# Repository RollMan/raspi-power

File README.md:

# Raspi-Power
## What is this?
This circuit keeps power supply to a raspberry pi for a second after the main power is down to shut down safely.. The functionalities are almost same as a UPS, but this is specialized to mount a car. This is useful for broadcasting your driving scenary, for example.

## How it works?
A car has two (strictly three) outlets: direct to battery and ACC. After you turn off an engine, ACC also turns off. This circuit detects that, and keep the power from battery directly while the raspberry pi is shutting down.

## Environment
- [kicad](http://kicad-pcb.org/) to see this circuit

## Misc
- A OKL\_T footprint thanks to (stm32f1/stm32-board)[https://github.com/stm32f1/stm32_board]

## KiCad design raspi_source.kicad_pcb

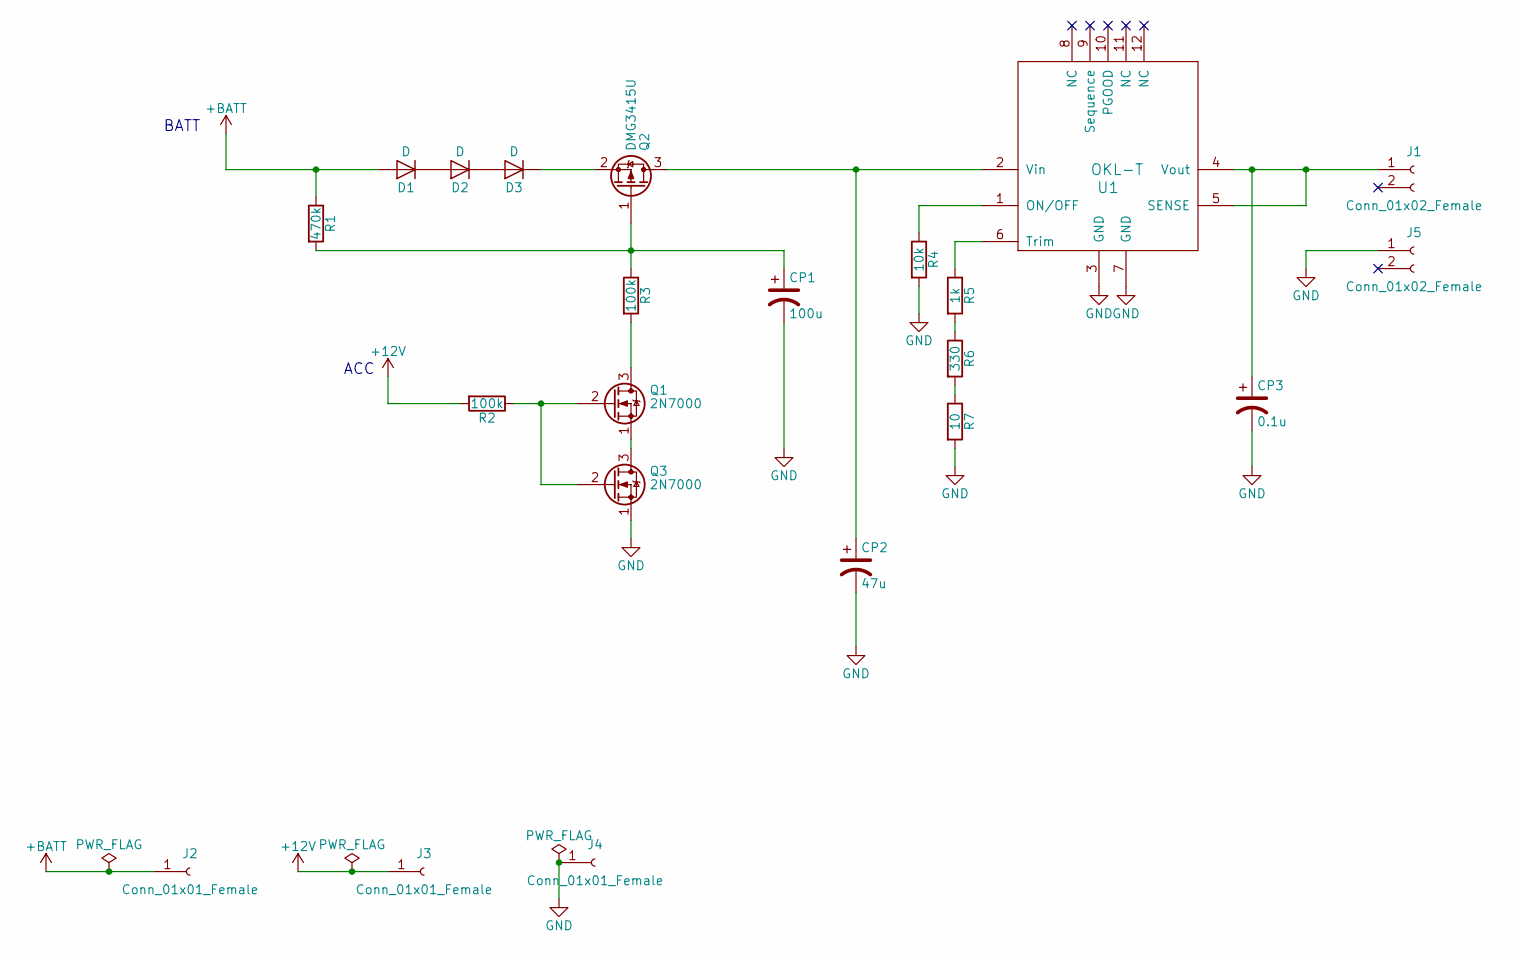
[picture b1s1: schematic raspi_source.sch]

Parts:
CP1: 100u; CP_Radial_Tantal_D4.5mm_P2.50mm
CP2: 47u; CP_Radial_Tantal_D4.5mm_P2.50mm
CP3: 0.1u; CP_Radial_Tantal_D4.5mm_P2.50mm
D1, D2, D3: D; D_A-405_P7.62mm_Horizontal
J1, J5: Conn_01x02_Female; Socket_Strip_Straight_1x02_Pitch2.54mm
J2, J3, J4: Conn_01x01_Female; Socket_Strip_Straight_1x01_Pitch2.54mm
Q1, Q3: 2N7000; TO-92_Molded_Narrow
Q2: DMG3415U; SOT-23
R1: 470k; R_Axial_DIN0204_L3.6mm_D1.6mm_P7.62mm_Horizontal
R2, R3: 100k; R_Axial_DIN0204_L3.6mm_D1.6mm_P7.62mm_Horizontal
R4: 10k; R_Axial_DIN0204_L3.6mm_D1.6mm_P7.62mm_Horizontal
R5: 1k; R_Axial_DIN0204_L3.6mm_D1.6mm_P7.62mm_Horizontal
R6: 330; R_Axial_DIN0204_L3.6mm_D1.6mm_P7.62mm_Horizontal
R7: 10; R_Axial_DIN0204_L3.6mm_D1.6mm_P7.62mm_Horizontal
U1: OKL-T; OKL_T6

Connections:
+12V: J3.1, R2.2
+BATT: D1.2 (A), J2.1, R1.1
GND: CP1.2, CP2.2, CP3.2, J4.1, J5.1, Q3.1 (S), R4.2, R7.2, U1.3 (GND), U1.7 (GND)
unnamed: CP1.1, Q2.1 (G), R1.2, R3.1
unnamed: CP2.1, Q2.3 (D), U1.2 (Vin)
unnamed: CP3.1, J1.1, U1.4 (Vout), U1.5 (SENSE)
unnamed: D1.1 (K), D2.2 (A)
unnamed: D2.1 (K), D3.2 (A)
unnamed: D3.1 (K), Q2.2 (S)
unnamed: Q1.1 (S), Q3.3 (D)
unnamed: Q1.2 (G), Q3.2 (G), R2.1
unnamed: Q1.3 (D), R3.2
unnamed: R4.1, U1.1 (ON/OFF)
unnamed: R5.1, U1.6 (Trim)
unnamed: R5.2, R6.1
unnamed: R6.2, R7.1

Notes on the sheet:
ACC
BATT

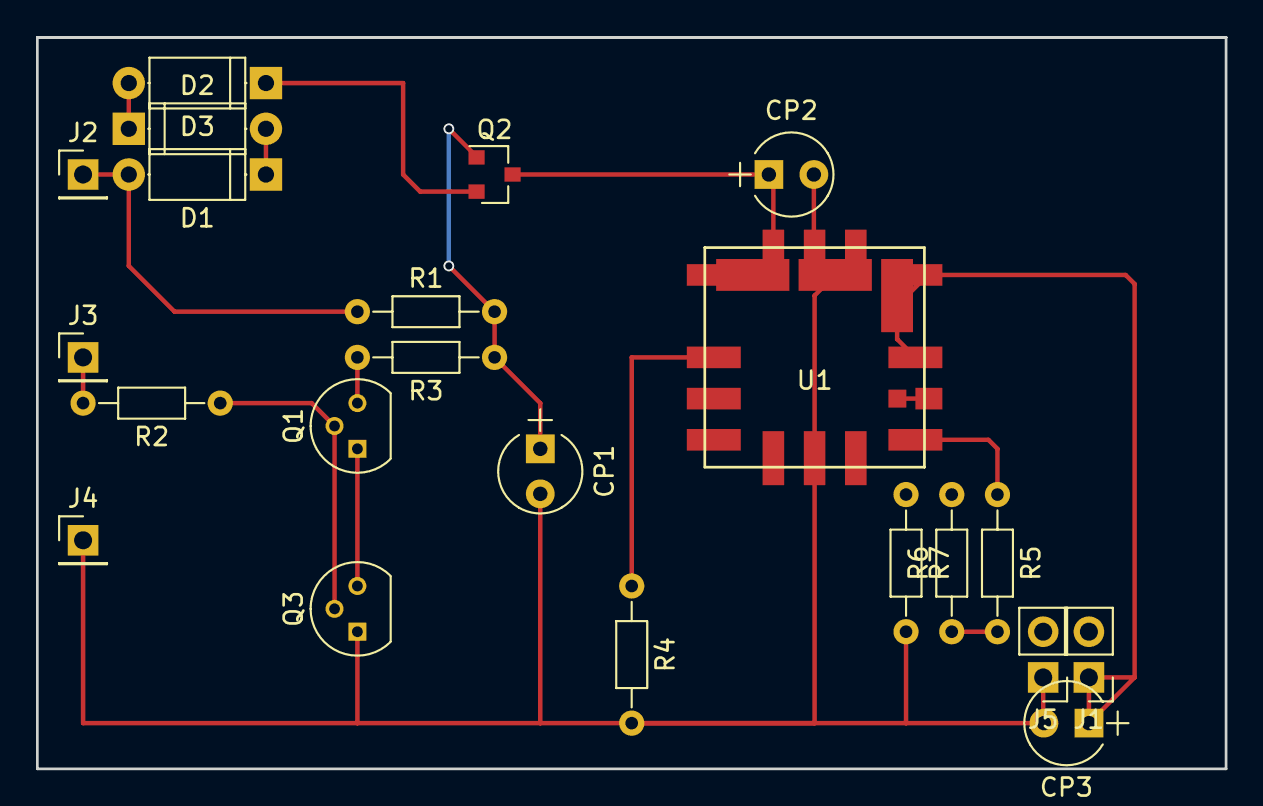
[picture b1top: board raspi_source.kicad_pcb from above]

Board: 2 copper layers, 66.0 x 40.6 mm, 22 parts (0 on the bottom side), 16 nets.

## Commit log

2018-06-03 initial commit
    schematic had been created
2018-06-03 add radme
2018-06-07 add optimized_register_calculator
2018-06-09 the scheme has been complete.
    test has been passed and the scheme was modified
2018-06-10 adjust dcdc register
2018-06-10 add footprint of new components
2018-06-10 expand footprints
2018-06-10 wiring has been completed
2018-06-10 move capaciter
2018-06-10 fix something
    TODO: need find what i fixed
2019-03-23 add README
